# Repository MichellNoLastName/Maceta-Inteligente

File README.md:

# 🌱 Maceta Inteligente para el Crecimiento de un Crisantemo

Este proyecto fue desarrollado como parte de la asignatura **Proyecto Integrador**, con el objetivo de diseñar y programar una **maceta inteligente** que monitorea y controla las condiciones ambientales necesarias para el óptimo crecimiento de un **crisantemo**.  

La maceta integra sensores, un sistema de riego automático, control de luz artificial y una interfaz LCD para mostrar información en tiempo real, todo gestionado mediante un **Arduino**.

---

## 🚀 Características principales

- 📊 **Monitoreo de temperatura y humedad ambiental** mediante un sensor **DHT11**.  
- 💧 **Control automático de riego** con bomba de agua y sensores de nivel de tanque.  
- ☀️ **Control de fotoperiodo** mediante un sistema de iluminación artificial, activado según el ciclo programado para la planta.  
- 🔔 **Alarmas sonoras** (buzzer) para advertencias de exceso/falta de agua, luz o temperatura.  
- 🖥️ **Pantalla LCD 20x4 con I2C**, que muestra:
  - Fecha y hora (RTC DS1307).  
  - Temperatura y humedad.  
  - Estado del tanque y la luz.  
  - Menú de configuración y selección de planta.  
- 🌼 **Base de datos de parámetros óptimos** para 3 plantas (incluyendo el crisantemo), con rangos de temperatura, humedad y fotoperiodo.  

---

## 🛠️ Componentes utilizados

- **Arduino UNO**  
- **Sensor DHT11** → temperatura y humedad ambiental  
- **Sensor de humedad de suelo** (analógico)  
- **Sensores de nivel de agua** (mínimo y máximo)  
- **Bomba de agua** + relevador para riego automático  
- **LED / lámpara de cultivo** para control de luminosidad  
- **Pantalla LCD 20x4 con módulo I2C**  
- **Módulo RTC DS1307** → control de fecha y hora  
- **Buzzer piezoeléctrico**  
- **Botones de navegación** (izquierda, derecha, enter)  

---

## 📋 Funcionalidades del software

1. **Selección de planta al inicio** (Crisantemo, Rosa de alabastro o Petunia).  
2. **Adquisición de datos en tiempo real** (temperatura, humedad, nivel de agua, fotoperiodo).  
3. **Acciones automáticas**:
   - Activa la bomba de riego si la humedad del suelo es baja.  
   - Activa o apaga la luz según el ciclo fotoperiódico de la planta seleccionada.  
   - Alarmas en caso de exceso de temperatura, sequedad extrema o falta de agua en el tanque.  
4. **Interfaz de usuario en LCD** con menús:
   - Estado actual del sistema.  
   - Parámetros de la planta seleccionada.  
   - Información del sustrato recomendado.  
   - Control manual de la luz.  
   - Activar o desactivar modo silencioso.  
5. **Uso de RTC DS1307** para el control exacto de horarios.  

---

## 📂 Estructura del código

El programa está desarrollado en **C++ para Arduino**, con las siguientes secciones principales:

- Configuración de **pines y sensores**.  
- Inicialización de **LCD y RTC**.  
- **Menú de selección de planta** al inicio.  
- **Loop principal**:
  - Lectura de sensores.  
  - Actualización de pantalla LCD.  
  - Ejecución de alarmas y acciones automáticas.  
- Funciones auxiliares:
  - `read_ds1307()` → lectura del reloj en tiempo real.  
  - `bcd2bin()` → conversión de valores BCD.  
  - `antireboot()` → debounce de botones.  

---

## 📊 Parámetros configurados para el Crisantemo

- 🌡️ **Temperatura óptima**: 10°C – 32°C  
- 💧 **Humedad óptima del suelo**: 65% – 70%  
- ☀️ **Fotoperiodo**: 7:00 a 18:00  
- 🌱 **Sustrato recomendado**:  
  - 2/3 tierra de jardín  
  - 1/3 composta  

---

## 📸 Ejemplo del flujo de trabajo

1. Al encender el sistema, el usuario selecciona la planta en el menú LCD.  
2. El sistema comienza a **monitorear los sensores** y controla automáticamente el riego y la luz.  
3. Si la planta está en riesgo (frío, calor, exceso de agua, falta de tanque), se activa el **buzzer y mensajes en LCD**.  
4. El usuario puede navegar en el menú para ver información o activar/desactivar funciones manualmente.  

---

## 📌 Futuras mejoras

- Comunicación con una **aplicación móvil** vía Bluetooth o WiFi.  
- Registro de datos en **tarjeta SD** para análisis histórico.  
- Implementación de un **modo automático de aprendizaje** que ajuste parámetros según el crecimiento real de la planta.  

---

## 👨‍💻 Autores

Este proyecto fue desarrollado por estudiantes de la asignatura **Proyecto Integrador**, con el objetivo de aplicar conocimientos en:  
- Programación de microcontroladores.  
- Electrónica y sensores.  
- Automatización y control ambiental.  

---
📖 **Asignatura:** Proyecto Integrador  
🌼 **Planta principal de estudio:** Crisantemo  
⚡ **Tecnologías usadas:** Arduino, C++, Electrónica de control

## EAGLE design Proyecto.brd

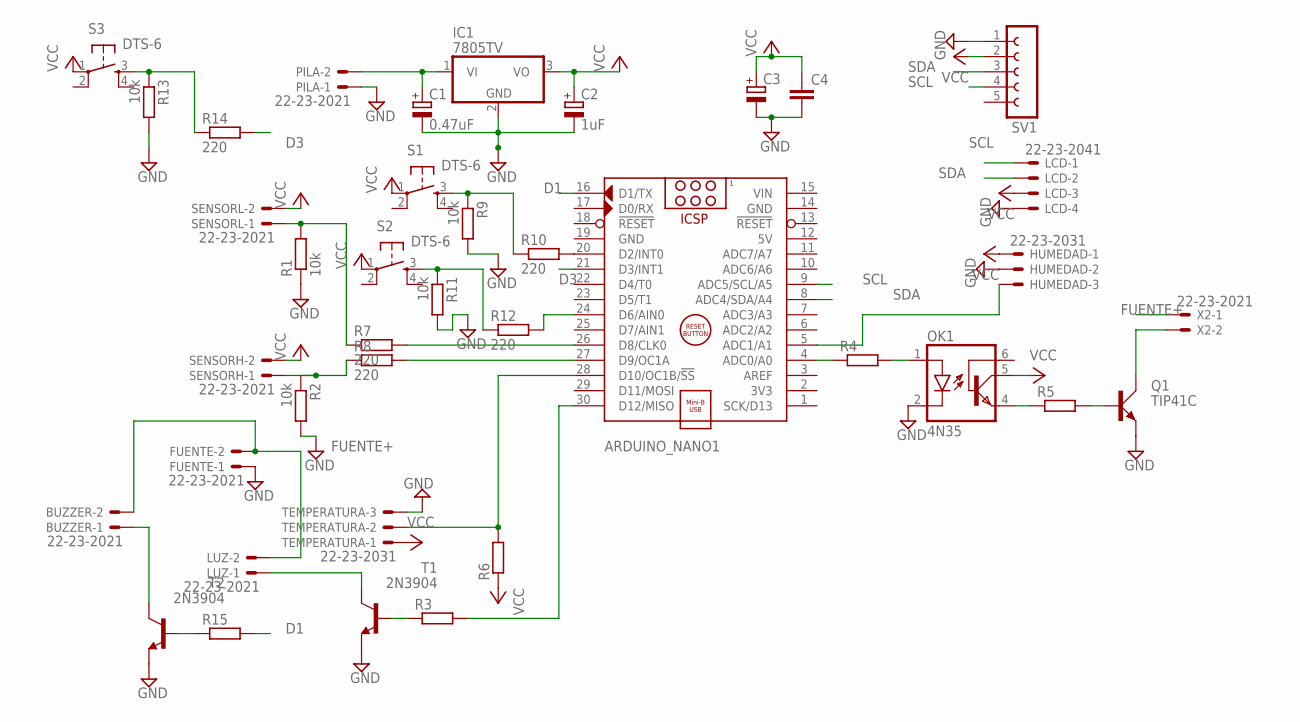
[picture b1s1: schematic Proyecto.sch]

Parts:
ARDUINO_NANO1: ARDUINO_NANO
BUZZER: 22-23-2021
C1: 0.47uF; E1,8-4
C2: 1uF; E1,8-4
C3: CPOL-EUE3.5-10; E3,5-10
C4: C-EU025-040X050; C025-040X050
FUENTE: 22-23-2021
HUMEDAD: 22-23-2031
IC1: 7805TV; TO220V
LCD: 22-23-2041
LUZ: 22-23-2021
OK1: 4N35; DIL06
PILA: 22-23-2021
Q1: TIP41C; TO220AV
R1, R2, R9, R11, R13: 10k; 0207/10
R3, R4, R5, R6, R15: R-EU_0207/10; 0207/10
R7, R8, R10, R12, R14: 220; 0207/10
S1, S2, S3: DTS-6
SENSORH: 22-23-2021
SENSORL: 22-23-2021
SV1: FE05-1
T1, T2: 2N3904; TO92
TEMPERATURA: 22-23-2031
X2: 22-23-2021

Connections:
5V: ARDUINO_NANO1.12 (5V)
D1: ARDUINO_NANO1.16 (D1/TX), R15.2
D3: ARDUINO_NANO1.21 (D3/INT1), R14.2
FUENTE+: BUZZER.2, FUENTE.2, LUZ.2, X2.1
GND: ARDUINO_NANO1.14 (GND), ARDUINO_NANO1.19 (GND), C1.-, C2.-, C3.-, C4.2, FUENTE.1, HUMEDAD.2, IC1.2 (GND), LCD.4, OK1.2 (C), PILA.1, Q1.E, R1.1, R2.2, R9.2, R11.2, R13.2, SV1.1, T1.3 (E), T2.3 (E), TEMPERATURA.3
unnamed: ARDUINO_NANO1.28 (D10/OC1B/!SS), R6.2, TEMPERATURA.2
unnamed: R1.2, R7.1, SENSORL.1
unnamed: R2.1, R8.1, SENSORH.1
unnamed: LUZ.1, T1.1 (C)
unnamed: R3.1, T1.2 (B)
unnamed: ARDUINO_NANO1.30 (D12/MISO), R3.2
unnamed: Q1.B, R5.2
unnamed: OK1.4 (EMI), R5.1
unnamed: Q1.C, X2.2
unnamed: OK1.1 (A), R4.2
unnamed: ARDUINO_NANO1.4 (ADC0/A0), R4.1
unnamed: ARDUINO_NANO1.27 (D9/OC1A), R8.2
unnamed: ARDUINO_NANO1.26 (D8/CLK0), R7.2
unnamed: C1.+, IC1.1 (VI), PILA.2
unnamed: ARDUINO_NANO1.5 (ADC1/A1), HUMEDAD.3
unnamed: R9.1, R10.1, S1.3
unnamed: ARDUINO_NANO1.20 (D2/INT0), R10.2
unnamed: R11.1, R12.1, S2.3
unnamed: ARDUINO_NANO1.24 (D6/AIN0), R12.2
unnamed: R13.1, R14.1, S3.3
unnamed: BUZZER.1, T2.1 (C)
unnamed: R15.1, T2.2 (B)
SCL: ARDUINO_NANO1.9 (ADC5/SCL/A5), LCD.1, SV1.4
SDA: ARDUINO_NANO1.8 (ADC4/SDA/A4), LCD.2, SV1.3
VCC: C2.+, C3.+, C4.1, HUMEDAD.1, IC1.3 (VO), LCD.3, OK1.5 (COL), R6.1, S1.1, S2.1, S3.1, SENSORH.2, SENSORL.2, SV1.2, TEMPERATURA.1
VIN: ARDUINO_NANO1.15 (VIN)

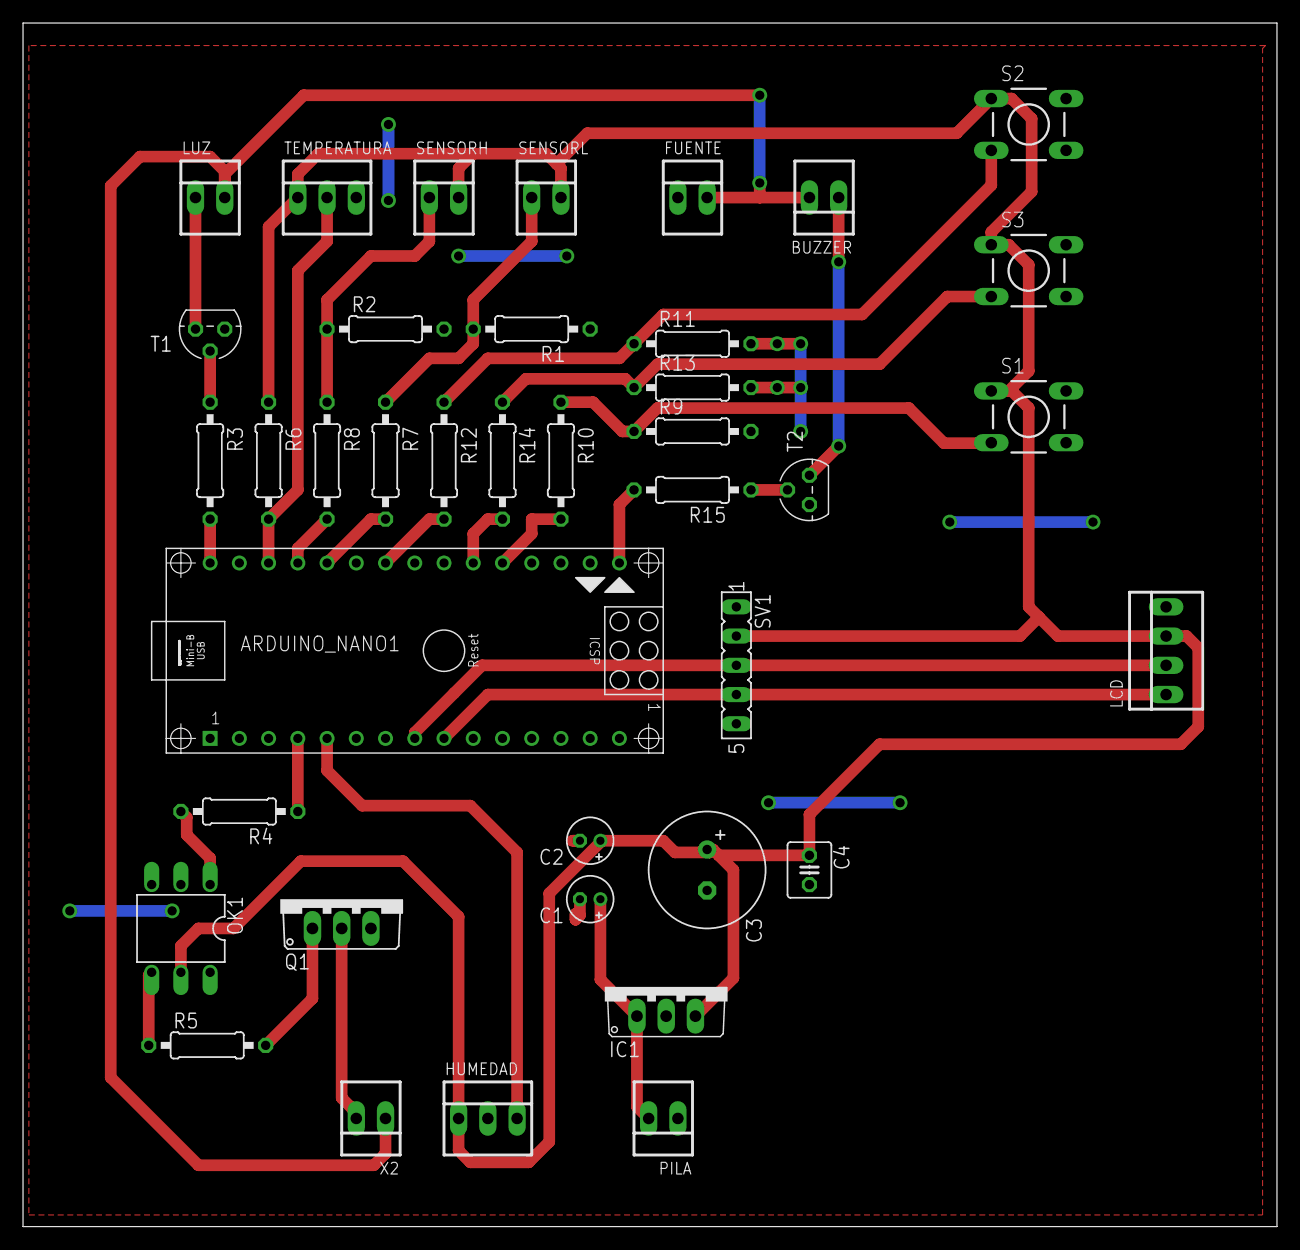
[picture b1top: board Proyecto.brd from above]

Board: 2 copper layers, 108.9 x 104.6 mm, 39 parts (0 on the bottom side), 29 nets.

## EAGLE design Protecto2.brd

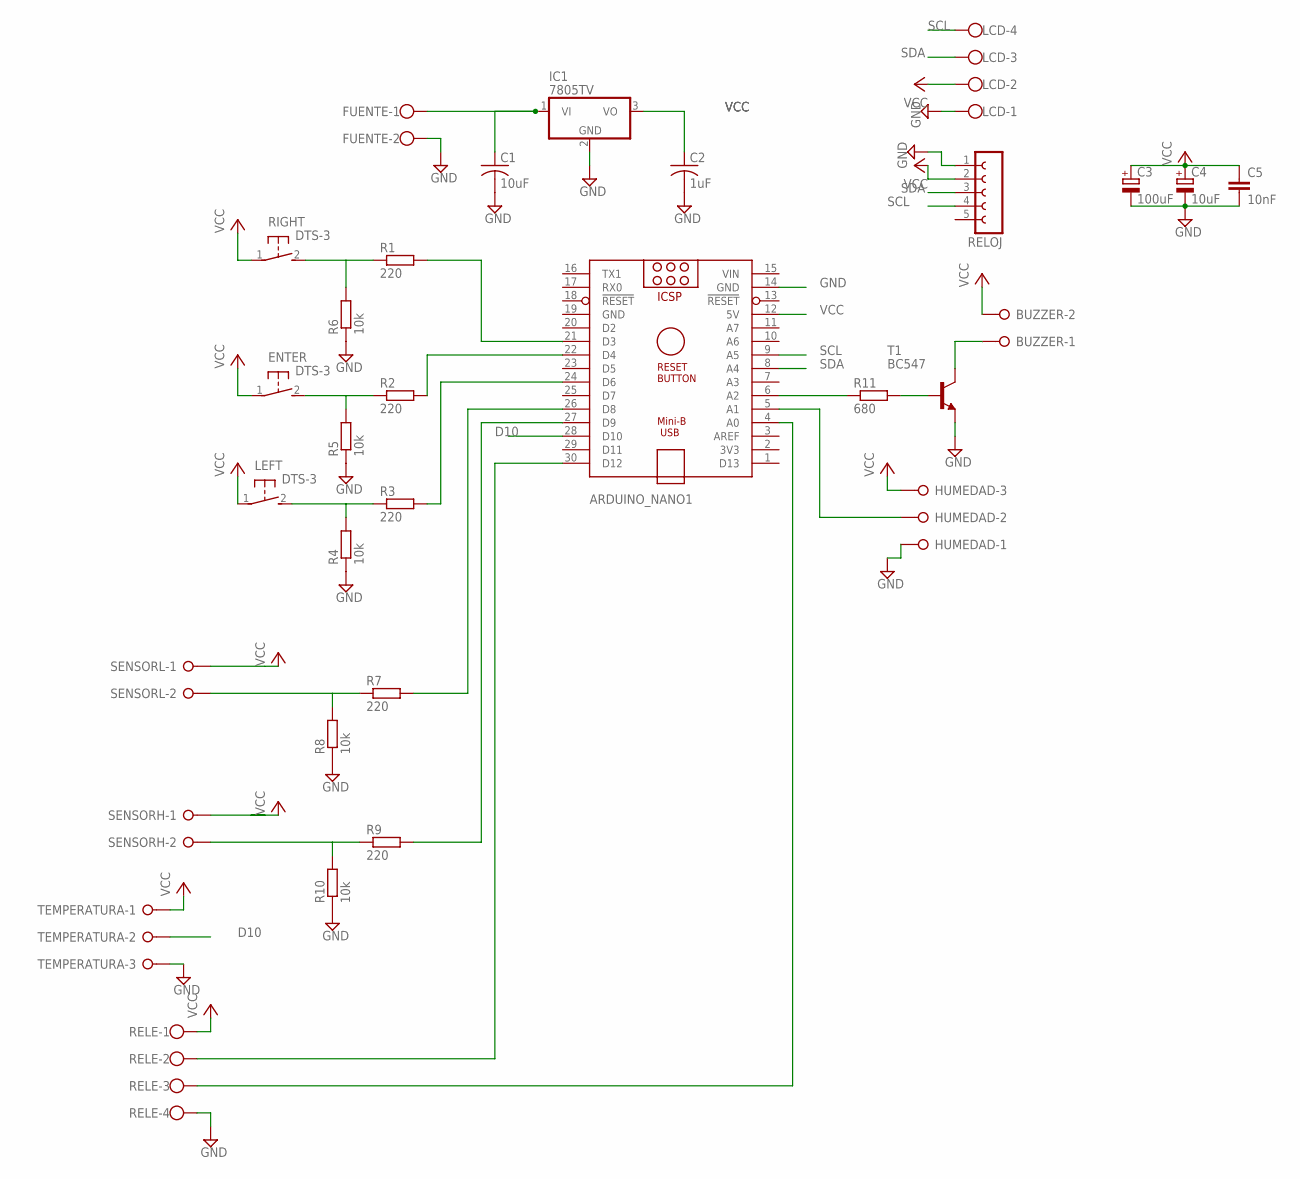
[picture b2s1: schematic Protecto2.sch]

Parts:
ARDUINO_NANO1: ARDUINO_NANO
BUZZER: W237-02P; W237-132
C1: 10uF; C025-040X050
C2: 1uF; C025-040X050
C3: 100uF; E2,5-7
C4: 10uF; E2-5
C5: 10nF; C025-030X050
ENTER: DTS-3
FUENTE: W237-102
HUMEDAD: W237-3E
IC1: 7805TV; TO220V
LCD: W237-4
LEFT: DTS-3
R1, R2, R3, R7, R9: 220; 0207/10
R4, R5, R6, R8, R10: 10k; 0207/10
R11: 680; 0207/10
RELE: W237-4
RELOJ: FE05-1
RIGHT: DTS-3
SENSORH: W237-02P; W237-132
SENSORL: W237-02P; W237-132
T1: BC547; TO92
TEMPERATURA: W237-3E

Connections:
D10: ARDUINO_NANO1.28 (D10), TEMPERATURA.2
GND: ARDUINO_NANO1.14 (GND), ARDUINO_NANO1.19 (GND), C1.2, C2.2, C3.-, C4.-, C5.2, FUENTE.2, HUMEDAD.1, IC1.2 (GND), LCD.1, R4.1, R5.1, R6.1, R8.1, R10.1, RELE.4, RELOJ.1, T1.1 (E), TEMPERATURA.3
unnamed: R1.1, R6.2, RIGHT.2
unnamed: ENTER.2, R2.1, R5.2
unnamed: LEFT.2, R3.1, R4.2
unnamed: ARDUINO_NANO1.21 (D3), R1.2
unnamed: ARDUINO_NANO1.22 (D4), R2.2
unnamed: ARDUINO_NANO1.24 (D6), R3.2
unnamed: R7.1, R8.2, SENSORL.2
unnamed: R9.1, R10.2, SENSORH.2
unnamed: ARDUINO_NANO1.26 (D8), R7.2
unnamed: ARDUINO_NANO1.27 (D9), R9.2
unnamed: ARDUINO_NANO1.4 (A0), RELE.3
unnamed: ARDUINO_NANO1.30 (D12), RELE.2
unnamed: ARDUINO_NANO1.5 (A1), HUMEDAD.2
unnamed: BUZZER.1, T1.3 (C)
unnamed: R11.2, T1.2 (B)
unnamed: ARDUINO_NANO1.6 (A2), R11.1
unnamed: C1.1, FUENTE.1, IC1.1 (VI)
SCL: ARDUINO_NANO1.9 (A5), LCD.4, RELOJ.4
SDA: ARDUINO_NANO1.8 (A4), LCD.3, RELOJ.3
VCC: ARDUINO_NANO1.12 (5V), BUZZER.2, C2.1, C3.+, C4.+, C5.1, ENTER.1, HUMEDAD.3, IC1.3 (VO), LCD.2, LEFT.1, RELE.1, RELOJ.2, RIGHT.1, SENSORH.1, SENSORL.1, TEMPERATURA.1
VIN: ARDUINO_NANO1.15 (VIN)

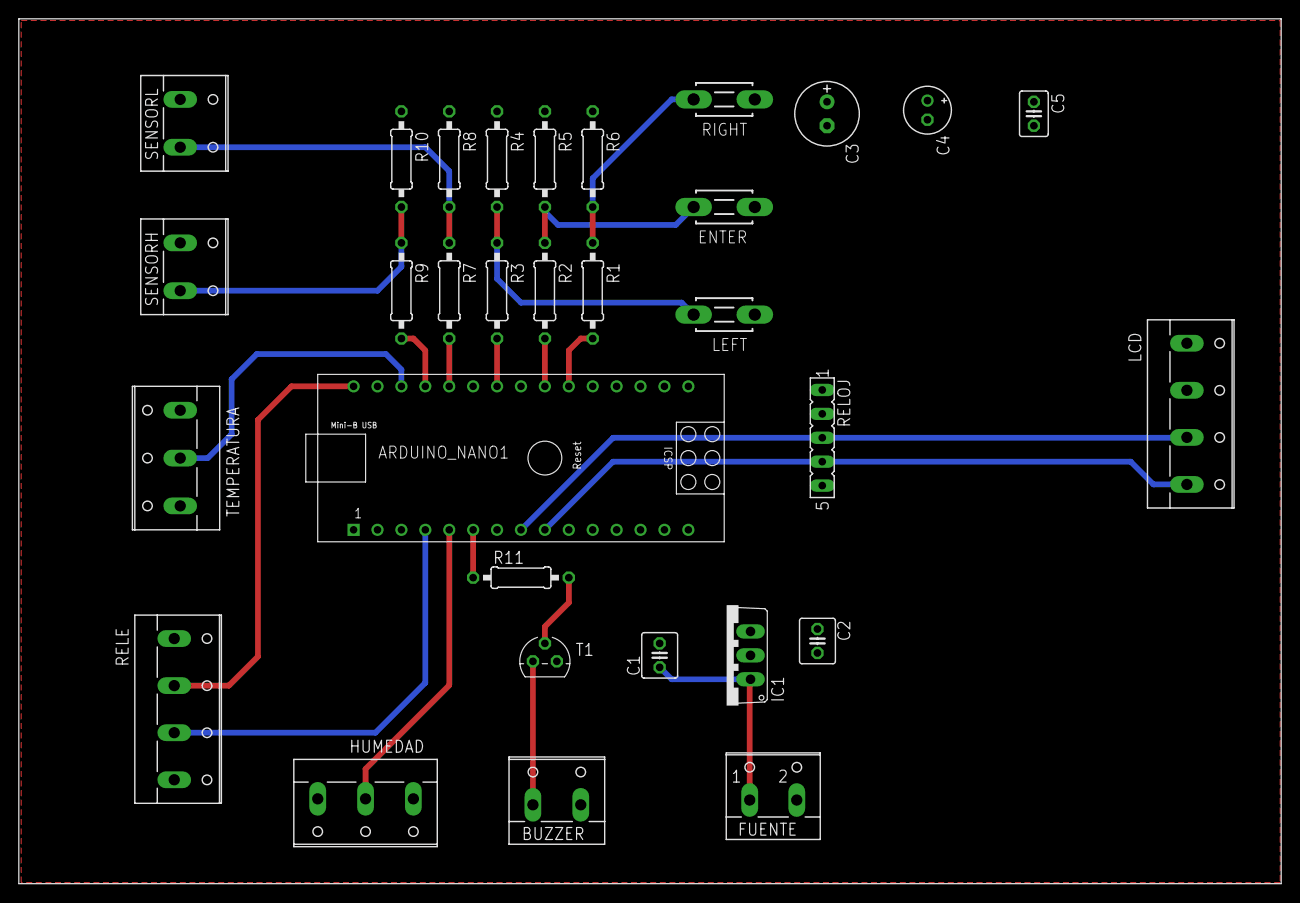
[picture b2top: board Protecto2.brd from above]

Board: 2 copper layers, 134.1 x 91.9 mm, 31 parts (0 on the bottom side), 22 nets.

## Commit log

2025-08-26 Carga de archivos del proyecto
2025-09-02 Se suben imagenes de proyecto
